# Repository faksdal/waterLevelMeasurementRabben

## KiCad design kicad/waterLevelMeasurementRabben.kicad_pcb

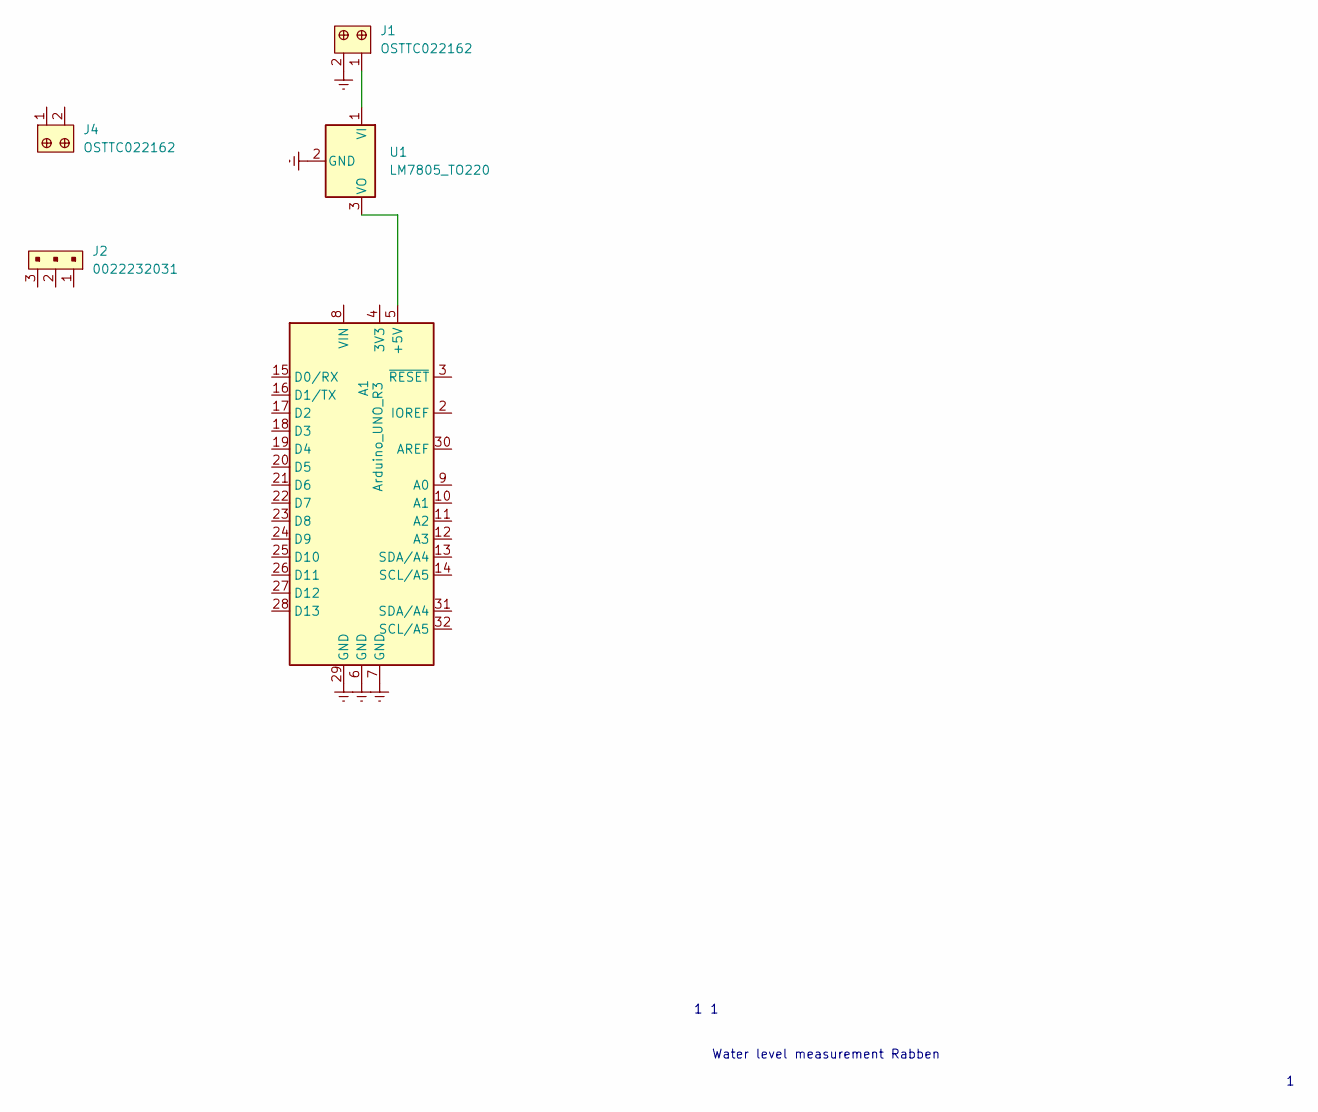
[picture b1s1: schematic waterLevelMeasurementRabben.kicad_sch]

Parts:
A1: Arduino_UNO_R3
J1, J4: OSTTC022162; Term_Block_1x2_P5.08MM; MPN OSTTC022162; Digi-Key_PN ED2609-ND
J2: 0022232031; PinHeader_1x3_P2.54mm_Drill1.02mm; MPN 0022232031; Digi-Key_PN WM4201-ND
U1: LM7805_TO220; TO-220-3_Vertical

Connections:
Earth: A1.6 (GND), A1.7 (GND), A1.29 (GND), J1.2, U1.2 (GND)
unnamed: A1.5 (+5V), U1.3 (VO)
unnamed: J1.1, U1.1 (VI)

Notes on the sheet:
Water level measurement Rabben

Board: 2 copper layers, 5 parts (0 on the bottom side), 3 nets, no tracks yet.
